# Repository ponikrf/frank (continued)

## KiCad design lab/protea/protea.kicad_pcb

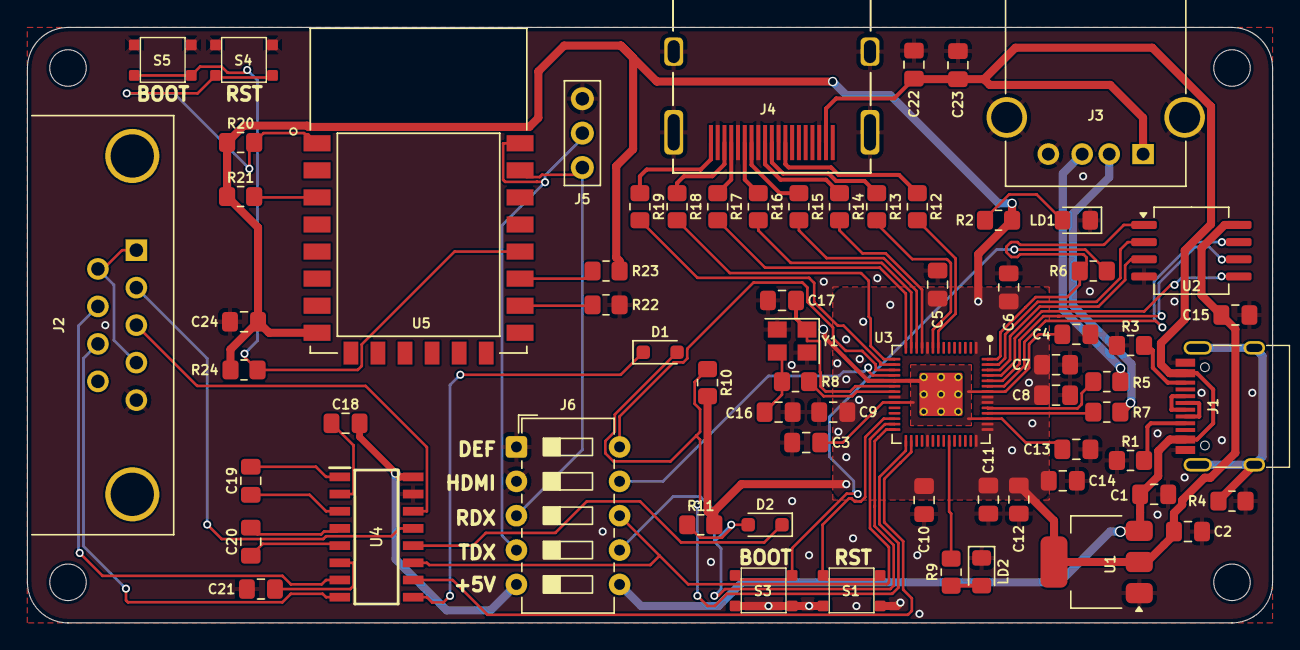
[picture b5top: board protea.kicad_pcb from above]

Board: 2 copper layers, 92.0 x 44.0 mm, 72 parts (0 on the bottom side), 70 nets.

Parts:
C1, C2, C22: 10u; Capacitor (0805)
C3, C4, C5, C6, C7, C8, C9, C10, C11, C12, C15, C23: 100n; Capacitor (0805)
C13, C14, C18, C19, C20, C21, C24: 1u; Capacitor (0805)
C16, C17: 15p; Capacitor (0805)
D1, D2: 1N4148; Diode (SOD-323)
H1, H2, H3, H4: MountingHole; Mounting Hole (2.7mm)
J1: USB4215-03-A; USB Type C
J2: D-SUB 9 Male; D-SUB (9 pin, male, top mount)
J3: 676430910; USB Type A (single)
J4: HDMI Female; HDMI (female)
J5: ESP8266 Prog; Pin Header (1x03)
J6: SD04H0SB; DIP Switch (5x5)
LD1: Green; LED (0805)
LD2: BLUE; LED (0805)
R1, R3: 5.1K; Resistor (0805)
R2, R6, R8, R9, R10, R11: 1K; Resistor (0805)
R4: 1M; Resistor (0805)
R5, R7: 27R; Resistor (0805)
R12, R13, R14, R15, R16, R17, R18, R19: 270R; Resistor (0805)
R20, R21, R22, R23, R24: 10K; Resistor (0805)
S1, S4: Reset; Button (SMD, 3x3mm, 1-1)
S3: Boot; Button (SMD, 3x3mm, 1-1)
S5: Flash; Button (SMD, 3x3mm, 1-1)
U1: NCP1117 3.3; SOT-223
U2: W25Q128JVSIQ; SOIC-8
U3: RP2040; QFN 56
U4: MAX232CSE+; SOIC127P600X175-16N
U5: ESP8266-12E_ESP-12E; ESP8266 ESP-12E
Y1: 12 MHz; Crystal (3225)

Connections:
+3V3: C2.1, C5.1, C6.1, C7.1, C8.1, C9.1, C10.1, C11.1, C12.1, C14.1, C15.1, C24.1, R2.2, R10.2, R11.2, R20.1, R21.1, R23.1, R24.1, U1.2 (VO), U2.8 (VCC), U3.1 (IOVDD), U3.10 (IOVDD), U3.22 (IOVDD), U3.33 (IOVDD), U3.42 (IOVDD), U3.43 (ADC_AVDD), U3.44 (VREG_IN), U3.48 (USB_VDD), U3.49 (IOVDD), U5.8 (VCC)
/D+: J3.3 (D+), R5.1
/D-: J3.2 (D-), R7.1
/ESP_RXD: J5.1, J6.5, U5.21 (RXD)
/ESP_TXD: J5.2, J6.7, U5.22 (TXD)
/GPIO6: R12.2, U3.8 (GPIO6)
/GPIO7: R13.2, U3.9 (GPIO7)
/GPIO8: R14.2, U3.11 (GPIO8)
/GPIO9: R15.2, U3.12 (GPIO9)
/GPIO10: R16.2, U3.13 (GPIO10)
/GPIO11: R17.2, U3.14 (GPIO11)
/GPIO12: R18.2, U3.15 (GPIO12)
/GPIO13: R19.2, U3.16 (GPIO13)
/GPIO14: J6.2, U3.17 (GPIO14)
/GPIO15: J6.4, U3.18 (GPIO15)
/GPIO16: J6.6, U3.27 (GPIO16), U4.11 (T1IN)
/GPIO17: D2.2 (A), J6.8, R11.1, U3.28 (GPIO17)
/GPIO18: D1.2 (A), R10.1, U3.29 (GPIO18)
/GPIO19: U3.30 (GPIO19), U4.10 (T2IN)
/Power/D+: J1.6 (DP1), J1.8 (DP2)
/Power/D-: J1.5 (DN2), J1.7 (DN1)
/RP2040/GPIO25: R9.2, U3.37 (GPIO25)
/RP2040/QSPI_SCLK: U2.6 (CLK), U3.52 (QSPI_SCLK)
/RP2040/QSPI_SD0: U2.5 (DI(IO0)), U3.53 (QSPI_SD0)
/RP2040/QSPI_SD1: U2.2 (DO(IO1)), U3.55 (QSPI_SD1)
/RP2040/QSPI_SD2: U2.3 (IO2), U3.54 (QSPI_SD2)
/RP2040/QSPI_SD3: U2.7 (IO3), U3.51 (QSPI_SD3)
/RP2040/QSPI_SS: R6.1, U2.1 (~CS), U3.56 (QSPI_SS)
/RP2040/XIN: C17.1, U3.20 (XIN), Y1.1
/RP2040/XOUT: R8.1, U3.21 (XOUT)
/RS232/C1+: C19.2, U4.1 (C1+)
/RS232/C1-: C19.1, U4.3 (C1-)
/RS232/C2+: C20.2, U4.4 (C2+)
/RS232/C2-: C20.1, U4.5 (C2-)
/RS232/CTS_IN: J2.7, U4.7 (T2OUT)
/RS232/CTS_MAX: D1.1 (K), U4.9 (R2OUT)
/RS232/RTS_IN: J2.8, U4.8 (R2IN)
/RS232/RX_IN: J2.3, U4.14 (T1OUT)
/RS232/RX_MAX: D2.1 (K), U4.12 (R1OUT)
/RS232/TX_IN: J2.2, U4.13 (R1IN)
/RS232/V+: C18.1, U4.2 (V+)
/RS232/V-: C21.1, U4.6 (V-)
/RS232_VBUS: C18.2, J6.9, U4.16 (VCC)
/RUN: S1.1, U3.26 (RUN)
GND: C1.2, C2.2, C3.2, C4.2, C5.2, C6.2, C7.2, C8.2, C9.2, C10.2, C11.2, C12.2, C13.2, C14.2, C15.2, C16.2, C17.2, C21.2, C22.1, C23.2, C24.2, J1.1 (GND), J1.12 (GND), J2.5, J3.4 (GND), J3.5 (Shield), J4.2 (G_D2), J4.5 (G_D1), J4.8 (G_D0), J4.11 (G_CLK), J4.17 (G_DDC/CEC), J4.20 (SHIELD1), J4.21 (SHIELD2), J4.22 (SHIELD3), J4.23 (SHIELD4), J5.3, J6.1, J6.3, LD1.1 (K), LD2.1 (K), R1.1, R3.1, R4.2, R22.1, S1.2, S3.2, S4.1, S5.1, U1.1 (GND), U2.4 (GND), U3.19 (TESTEN), U3.57 (GND), U4.15 (GND), Y1.2, Y1.4
unnamed: C16.1, R8.2, Y1.3
unnamed: J1.4 (CC1), R1.2
unnamed: J1.10 (CC2), R3.2
unnamed: J1.13 (SHIELD), R4.1
unnamed: J2.1, J2.4, J2.6
unnamed: J4.12 (CLKN), R12.1
unnamed: J4.10 (CLKP), R13.1
unnamed: J4.9 (D0N), R14.1
unnamed: J4.7 (D0P), R15.1
unnamed: J4.6 (D1N), R16.1
unnamed: J4.4 (D1P), R17.1
unnamed: J4.3 (D2N), R18.1
unnamed: J4.1 (D2P), R19.1
unnamed: LD1.2 (A), R2.1
unnamed: LD2.2 (A), R9.1
unnamed: R6.2, S3.1
unnamed: R7.2, U3.46 (USB_DM)
unnamed: R5.2, U3.47 (USB_DP)
unnamed: C3.1, C4.1, C13.1, U3.23 (DVDD), U3.45 (VREG_VOUT), U3.50 (DVDD)
unnamed: R21.2, U5.3 (EN)
unnamed: R24.2, S5.2, U5.18 (IO0)
unnamed: R23.2, U5.17 (IO2)
unnamed: R22.2, U5.16 (IO15)
unnamed: R20.2, S4.2, U5.1 (RESET)
VBUS: C1.1, C22.2, C23.1, J1.2 (VBUS), J1.11 (VBUS), J3.1 (VBUS), J4.18 (+5V), J6.10, U1.3 (VI)
